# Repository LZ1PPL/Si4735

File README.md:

# Reciver based on Si4735 and Si5351
The Si5351 is used as a local oscilator to create IF frequency of 10.7MHz. 
The demodulation of the signals and filters is achived in the Si4735.

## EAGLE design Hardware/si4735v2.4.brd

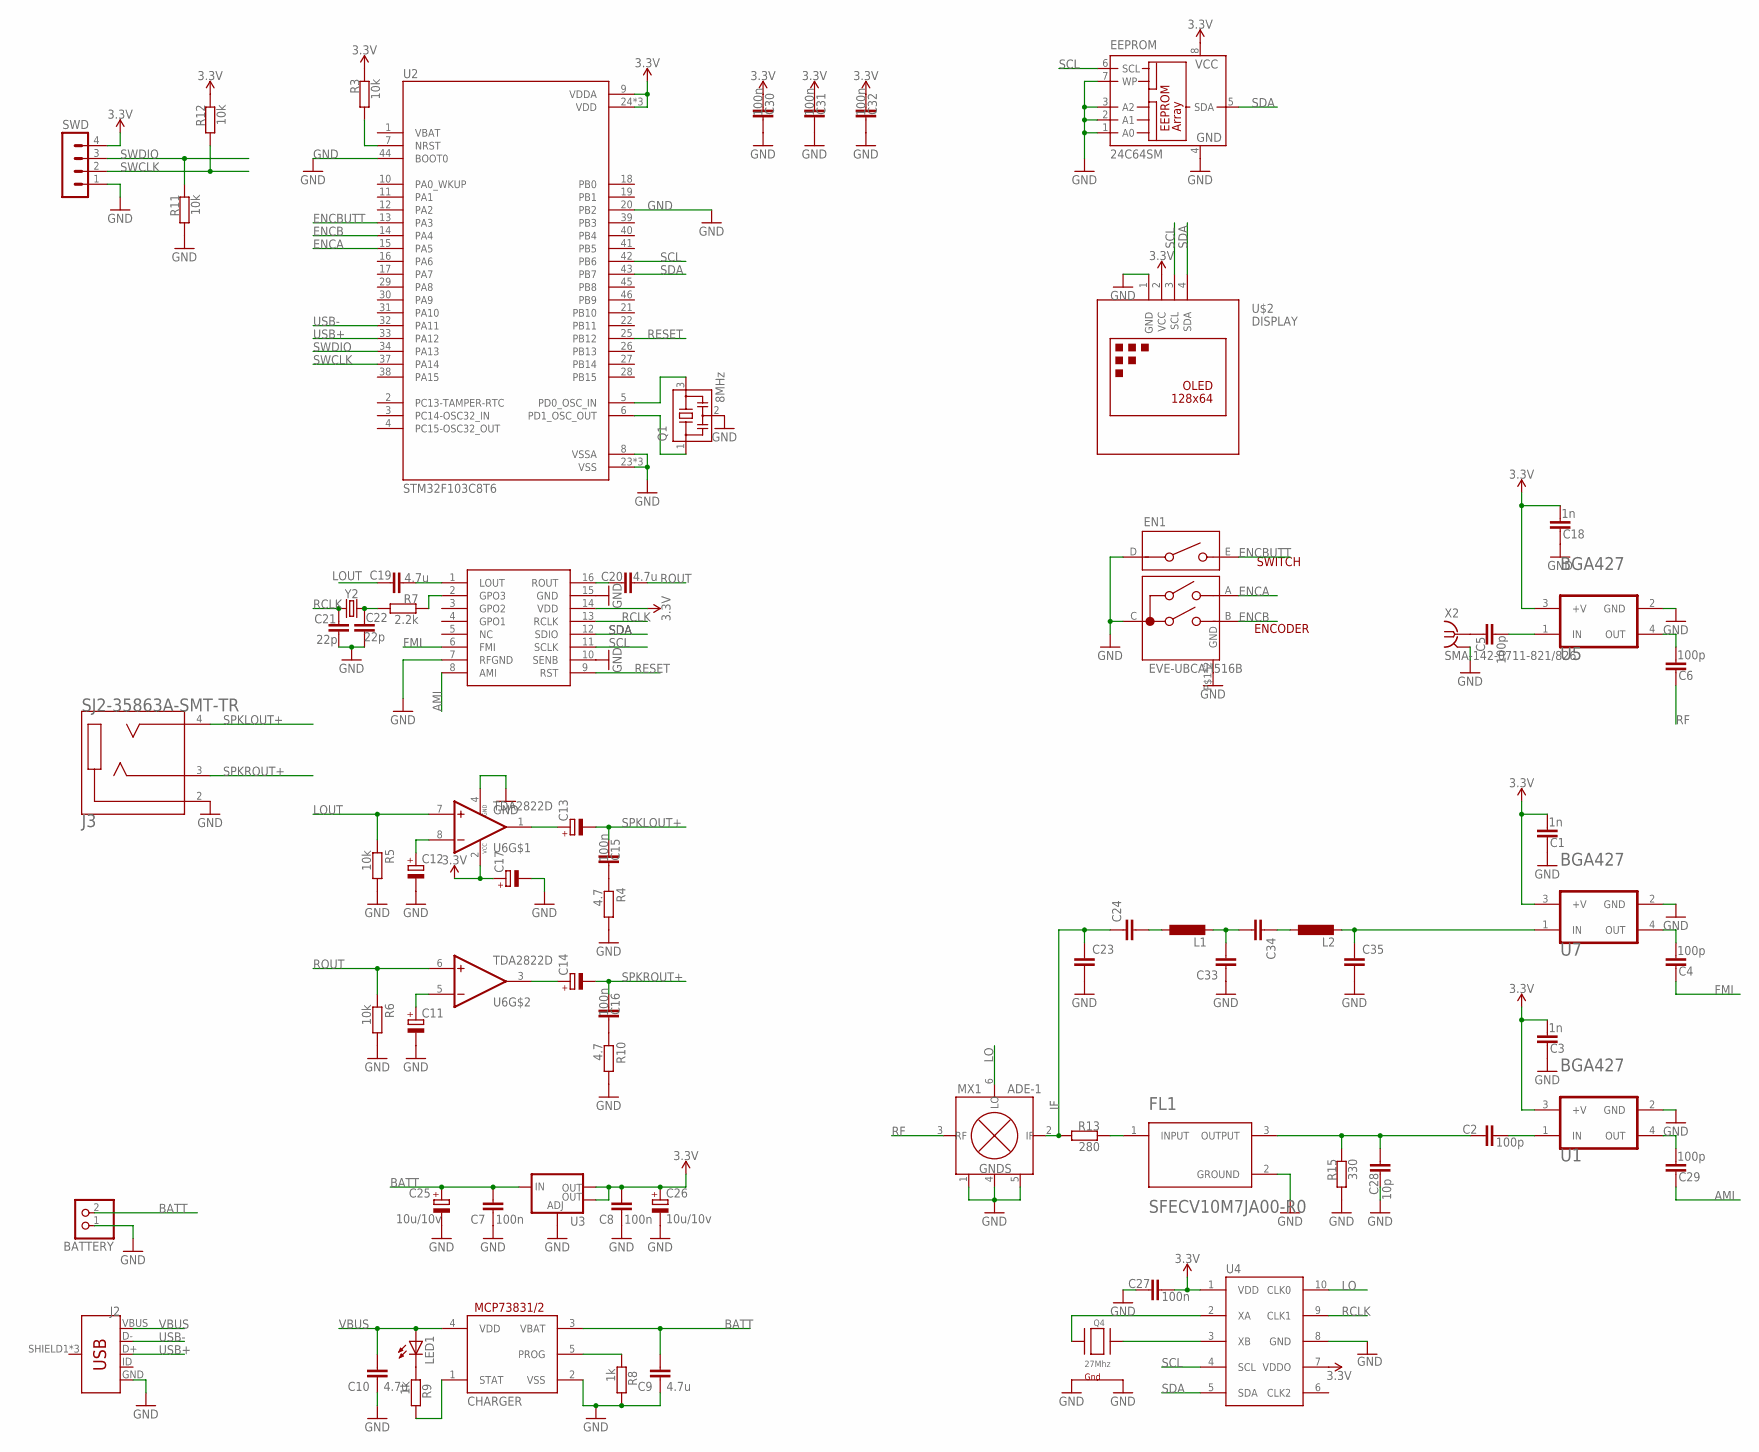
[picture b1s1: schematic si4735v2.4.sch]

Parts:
BATTERY: PINHD-1X2; 1X02
C1, C3, C18: 1n; C0805
C2, C4, C5, C6, C29: 100p; C0805
C7, C8, C15, C16, C27, C30, C31, C32: 100n; C0805
C9, C10, C19, C20: 4.7u; C0805
C11, C12, C13, C14: CPOL-EUSMCB; SMC_B
C17: CPOL-EUSMCA; SMC_A
C21, C22: 22p; C0805
C23, C24, C33, C34, C35: C-EUC0603; C0603
C25, C26: 10u/10v; A/3216-18W
C28: 10p; C0805
CHARGER: MCP73831/OT; SOT23-5L
EEPROM: 24C64SM; SO-08M
EN1: EVE-UBCAH516B
FL1: MURATA_ELECTRONICS_NORTH_AMERICA_SFECV10M7JA00-R0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; MURATA_ELECTRONICS_NORTH_AMERICA_SFECV10M7JA00-R0_0
J2: USB_MICRO-BREDUCED_PASTE; USB-B-MICRO-SMD_RED_PASTE
J3: SJ2-35863A-SMT-TR; CUI_SJ2-35863A-SMT-TR
L1, L2: L-EUL0603; L0603
LED1: LED3MM
MX1: ADE-1; CD636
Q1: 8MHz; CSTCR6M
Q4: 27Mhz; NX3225
R3, R5, R6, R11, R12: 10k; R0805
R4, R10: 4.7; R0805
R7: 2.2k; R0805
R8, R9: 1k; R0805
R13: 280; R0805
R15: 330; R0805
SI4732-A10: SI4732; SOIC127P600X175-16N
SWD: MA04-1
U1, U5, U7: INFINEON_BGA427INFINEON_BGA427_0_0; INFINEON_BGA427_0
U2: STM32F103C8T6; QFP50P900X900X160-48N
U3: V_REG_LM1117SOT223; SOT223
U4: SI5351A_CLOCK_GEN; MSOP-10
U6: TDA2822D; SOIC127P600X175-8N
U$2: DISPLAY; DISPLAY-OLED-128X64-I2C
X2: SMA-142-0711-821/826; J502-ND-142-0711-821/826
Y2: CRYSTALSMD-3.2X1.5; CRYSTAL-SMD-3.2X1.5MM

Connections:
3.3V: C1.1, C3.1, C8.2, C17.+, C18.1, C26.+, C27.1, C30.2, C31.2, C32.2, EEPROM.8 (VCC), R3.1, R12.1, SI4732-A10.14 (VDD), SWD.4, U1.3 (+V), U2.9 (VDDA), U2.24 (VDD), U2.36 (VDD), U2.48 (VDD), U3.2 (OUT), U3.4 (OUT), U4.1 (VDD), U4.7 (VDDO), U5.3 (+V), U6.2 (VCC), U7.3 (+V), U$2.2 (VCC)
AMI: C29.2, SI4732-A10.8 (AMI)
BATT: BATTERY.2, C7.2, C9.2, C25.+, CHARGER.3 (VBAT), U3.3 (IN)
ENCA: EN1.A, U2.15 (PA5)
ENCB: EN1.B, U2.14 (PA4)
ENCBUTT: EN1.E, U2.13 (PA3)
FILTER: C2.2, C28.1, FL1.3 (OUTPUT), R15.1
FMI: C4.2, SI4732-A10.6 (FMI)
GND: BATTERY.1, C1.2, C3.2, C7.1, C8.1, C9.1, C10.1, C11.-, C12.-, C17.-, C18.2, C21.1, C22.1, C23.2, C25.-, C26.-, C27.2, C28.2, C30.1, C31.1, C32.1, C33.1, C35.2, CHARGER.2 (VSS), EEPROM.1 (A0), EEPROM.2 (A1), EEPROM.3 (A2), EEPROM.4 (GND), EEPROM.7 (WP), EN1.C, EN1.D, EN1.P$1 (GND), EN1.P$2 (GND), FL1.2 (GROUND), J2.GND, J3.2 (SLEEVE), MX1.1 (GND), MX1.4 (GND), MX1.5 (GND), Q1.2, Q4.2 (G2), Q4.4 (G1), R4.2, R5.2, R6.2, R8.2, R10.2, R11.2, R15.2, SI4732-A10.7 (RFGND), SI4732-A10.10 (SENB), SI4732-A10.15 (GND), SWD.1, U1.2 (GND), U2.8 (VSSA), U2.20 (PB2), U2.23 (VSS), U2.35 (VSS), U2.44 (BOOT0), U2.47 (VSS), U3.1 (ADJ), U4.8 (GND), U5.2 (GND), U6.4 (GND), U7.2 (GND), U$2.1 (GND), X2.G@1 (2), X2.G@2 (2), X2.G@3 (2), X2.G@4 (2)
IF: C23.1, C24.1, MX1.2 (IF), R13.2
LO: MX1.6 (LO), U4.10 (CLK0)
LOUT: C19.2, R5.1, U6.7 (1IN+)
unnamed: Q1.3, U2.5 (PD0_OSC_IN)
unnamed: Q1.1, U2.6 (PD1_OSC_OUT)
unnamed: CHARGER.5 (PROG), R8.1
unnamed: C2.1, U1.1 (IN)
unnamed: C35.1, L2.2, U7.1 (IN)
unnamed: C6.1, U5.4 (OUT)
unnamed: C5.1, U5.1 (IN)
unnamed: C4.1, U7.4 (OUT)
unnamed: C12.+, U6.8 (1IN-)
unnamed: C11.+, U6.5 (2IN-)
unnamed: Q4.3 (X2), U4.3 (XB)
unnamed: C14.+, U6.3 (2OUT)
unnamed: Q4.1 (X1), U4.2 (XA)
unnamed: C13.+, U6.1 (1OUT)
unnamed: C15.1, R4.1
unnamed: C19.1, SI4732-A10.1 (LOUT)
unnamed: C20.1, SI4732-A10.16 (ROUT)
unnamed: C22.2, R7.2, Y2.P$2 (2)
unnamed: C16.1, R10.1
unnamed: R7.1, SI4732-A10.2 (GPO3)
unnamed: C5.2, X2.1
unnamed: C24.2, L1.1
unnamed: LED1.K (C), R9.1
unnamed: CHARGER.1 (STAT), R9.2
unnamed: C29.1, U1.4 (OUT)
unnamed: C33.2, C34.2, L1.2
unnamed: FL1.1 (INPUT), R13.1
unnamed: R3.2, U2.7 (NRST)
unnamed: C34.1, L2.1
RCLK: C21.2, SI4732-A10.13 (RCLK), U4.9 (CLK1), Y2.P$1 (1)
RESET: SI4732-A10.9 (RST), U2.25 (PB12)
RF: C6.2, MX1.3 (RF)
ROUT: C20.2, R6.1, U6.6 (2IN+)
SCL: EEPROM.6 (SCL), SI4732-A10.11 (SCLK), U2.42 (PB6), U4.4 (SCL), U$2.3 (SCL)
SDA: EEPROM.5 (SDA), SI4732-A10.12 (SDIO), U2.43 (PB7), U4.5 (SDA), U$2.4 (SDA)
SPKLOUT+: C13.-, C15.2, J3.4 (TIP)
SPKROUT+: C14.-, C16.2, J3.3 (RING)
SWCLK: R12.2, SWD.2, U2.37 (PA14)
SWDIO: R11.1, SWD.3, U2.34 (PA13)
USB+: J2.D+, U2.33 (PA12)
USB-: J2.D-, U2.32 (PA11)
VBUS: C10.2, CHARGER.4 (VDD), J2.VBUS, LED1.A

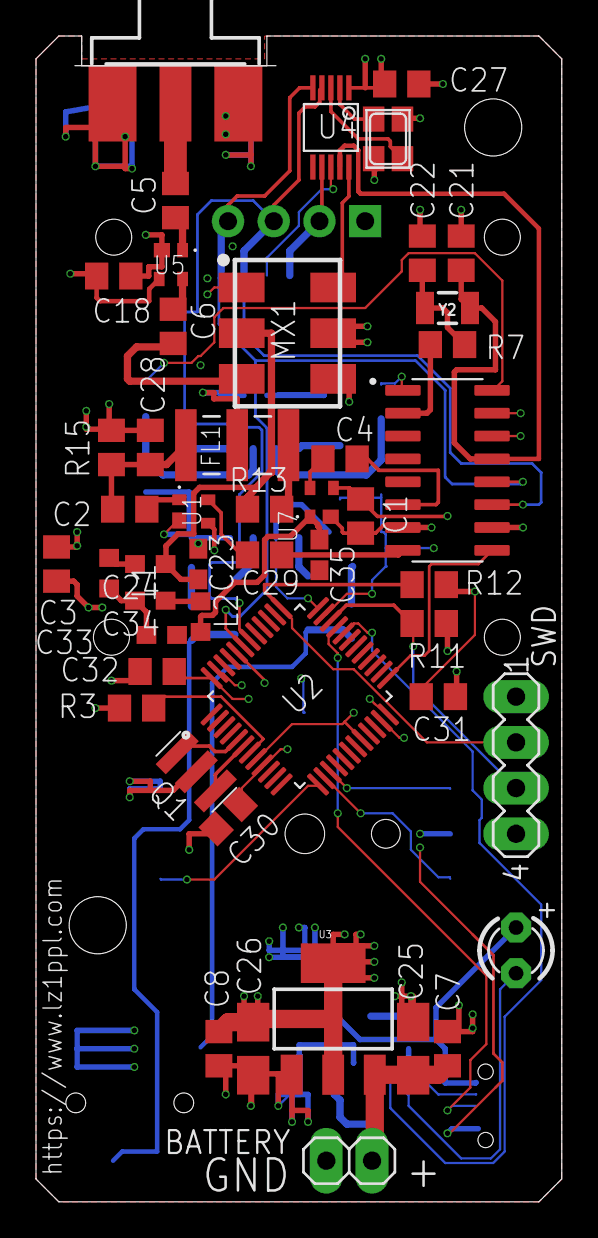
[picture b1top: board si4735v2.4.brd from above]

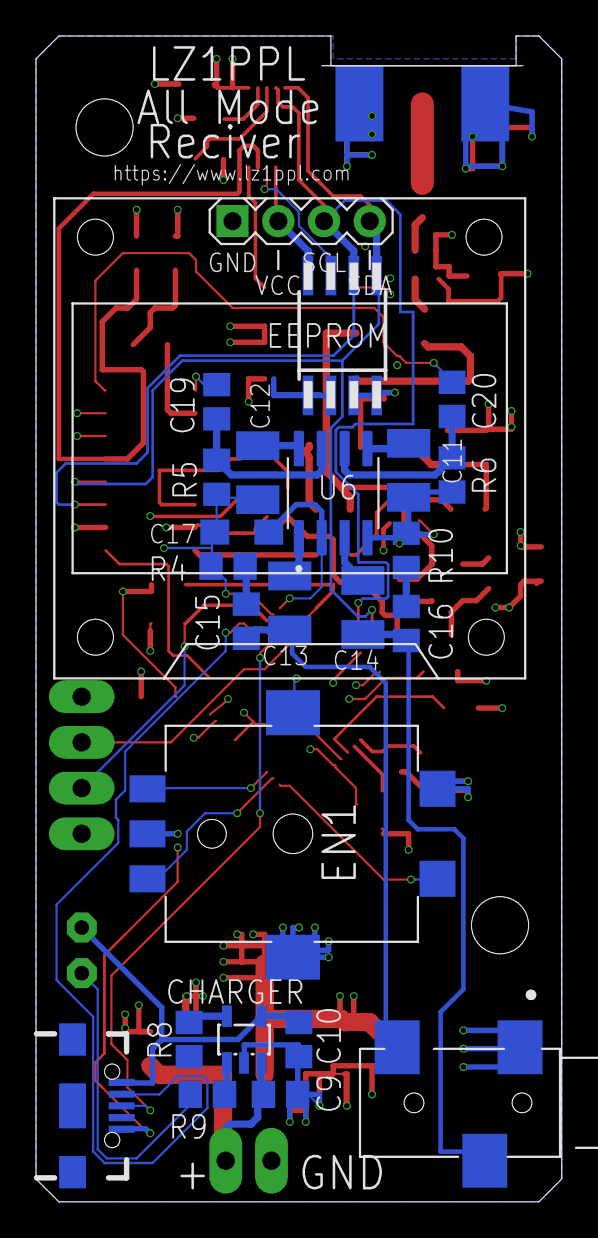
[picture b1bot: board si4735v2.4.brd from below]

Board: 4 copper layers, 29.2 x 64.8 mm, 72 parts (24 on the bottom side), 54 nets.

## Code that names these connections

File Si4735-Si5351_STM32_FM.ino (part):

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#define XT_CAL_F  39000       //Si5351 calibration factor, adjust to get exatcly 10MHz. 
#define XTAL_F  27000000      //Xtal frequency for Si5351
#define EEPROM_I2C_ADDR  0x50 // You might need to change this value
#define button PA3
#define RESET_PIN PB12

Adafruit_SSD1306 display(SCREEN_WIDTH, SCREEN_HEIGHT, &Wire, OLED_RESET);
Rotary r = Rotary(PA4, PA5);
SI4735 si4735;
Si5351 si5351(0x62);

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String steps;

void setup() {
  pinMode(PA4, INPUT_PULLUP);
  pinMode(PA5, INPUT_PULLUP);
  pinMode(PA3, INPUT_PULLUP);
  encoder0Pos = EEPROM.read(menuCount);
  display.begin(SSD1306_SWITCHCAPVCC, 0x3C);
  display.setTextColor(SSD1306_WHITE);
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  si4735.setSSBBfo(currentBFO);

  //si4735.setRefClock(32768);
  attachInterrupt(digitalPinToInterrupt(PA4), rot, CHANGE);
  attachInterrupt(digitalPinToInterrupt(PA5), rot, CHANGE);
  attachInterrupt(digitalPinToInterrupt(PA3), butt, FALLING);
}

void rot() {
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  delay (MIN_ELAPSED_TIME);
  elapsedCommand = millis();
  //firstv = millis();
  attachInterrupt(digitalPinToInterrupt(PA3), up, RISING);
}

void up()
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    firstv = secondv;
    EEPROM.put(10, freq);
  }
  attachInterrupt(digitalPinToInterrupt(PA3), butt, FALLING);
}

void loadSSB()
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
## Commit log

2021-04-27 Add files via upload
    Added Bandwidth filter for the FM mode
2021-06-22 Added BPF to the FMI input.
    PCB not tested yet.

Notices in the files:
parts and their libraries:
SparkFun-Connectors: Licensing: Creative Commons ShareAlike 4.0 International - https://creativecommons.org/licenses/by-sa/4.0
diy-modules: Released under the Creative Commons Attribution 4.0 International License: http://creativecommons.org/licenses/by/4.0
